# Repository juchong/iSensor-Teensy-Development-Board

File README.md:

# iSensor Teensy Development Board
### An open source development board for Analog Devices iSensor products

This development board was designed to provide users with an easy way to develop and test firmware using iSensor MEMS IMUs. The board conforms to the standard Arduino pinout making it compatible with the entire ecosystem of break-out boards. A Teensy 3.1, 3.2, or LC may be used with this board, minimizing cost. The board includes a standard 2mm pitch 16 pin connector similar to the BlackFin evaluation board, making all iSensor breakout boards compatible. 

The board includes the following features:
- 4V ~ 20V input, 3.3V output switching regulator with selectable input (USB vs External)
- Programmable high-side switch for controlled switching tests
- 3.3V external supply input
- I2C/Analog Input selectable solder pads
- Compatible with Arduino pinout and mechanical form factor

Note that the switching regulator is optional and does not have to be installed for the breakout board to properly function.

Click here to order a set of boards from OshPark: [https://oshpark.com/shared_projects/IdmggZVF](https://oshpark.com/shared_projects/IdmggZVF)

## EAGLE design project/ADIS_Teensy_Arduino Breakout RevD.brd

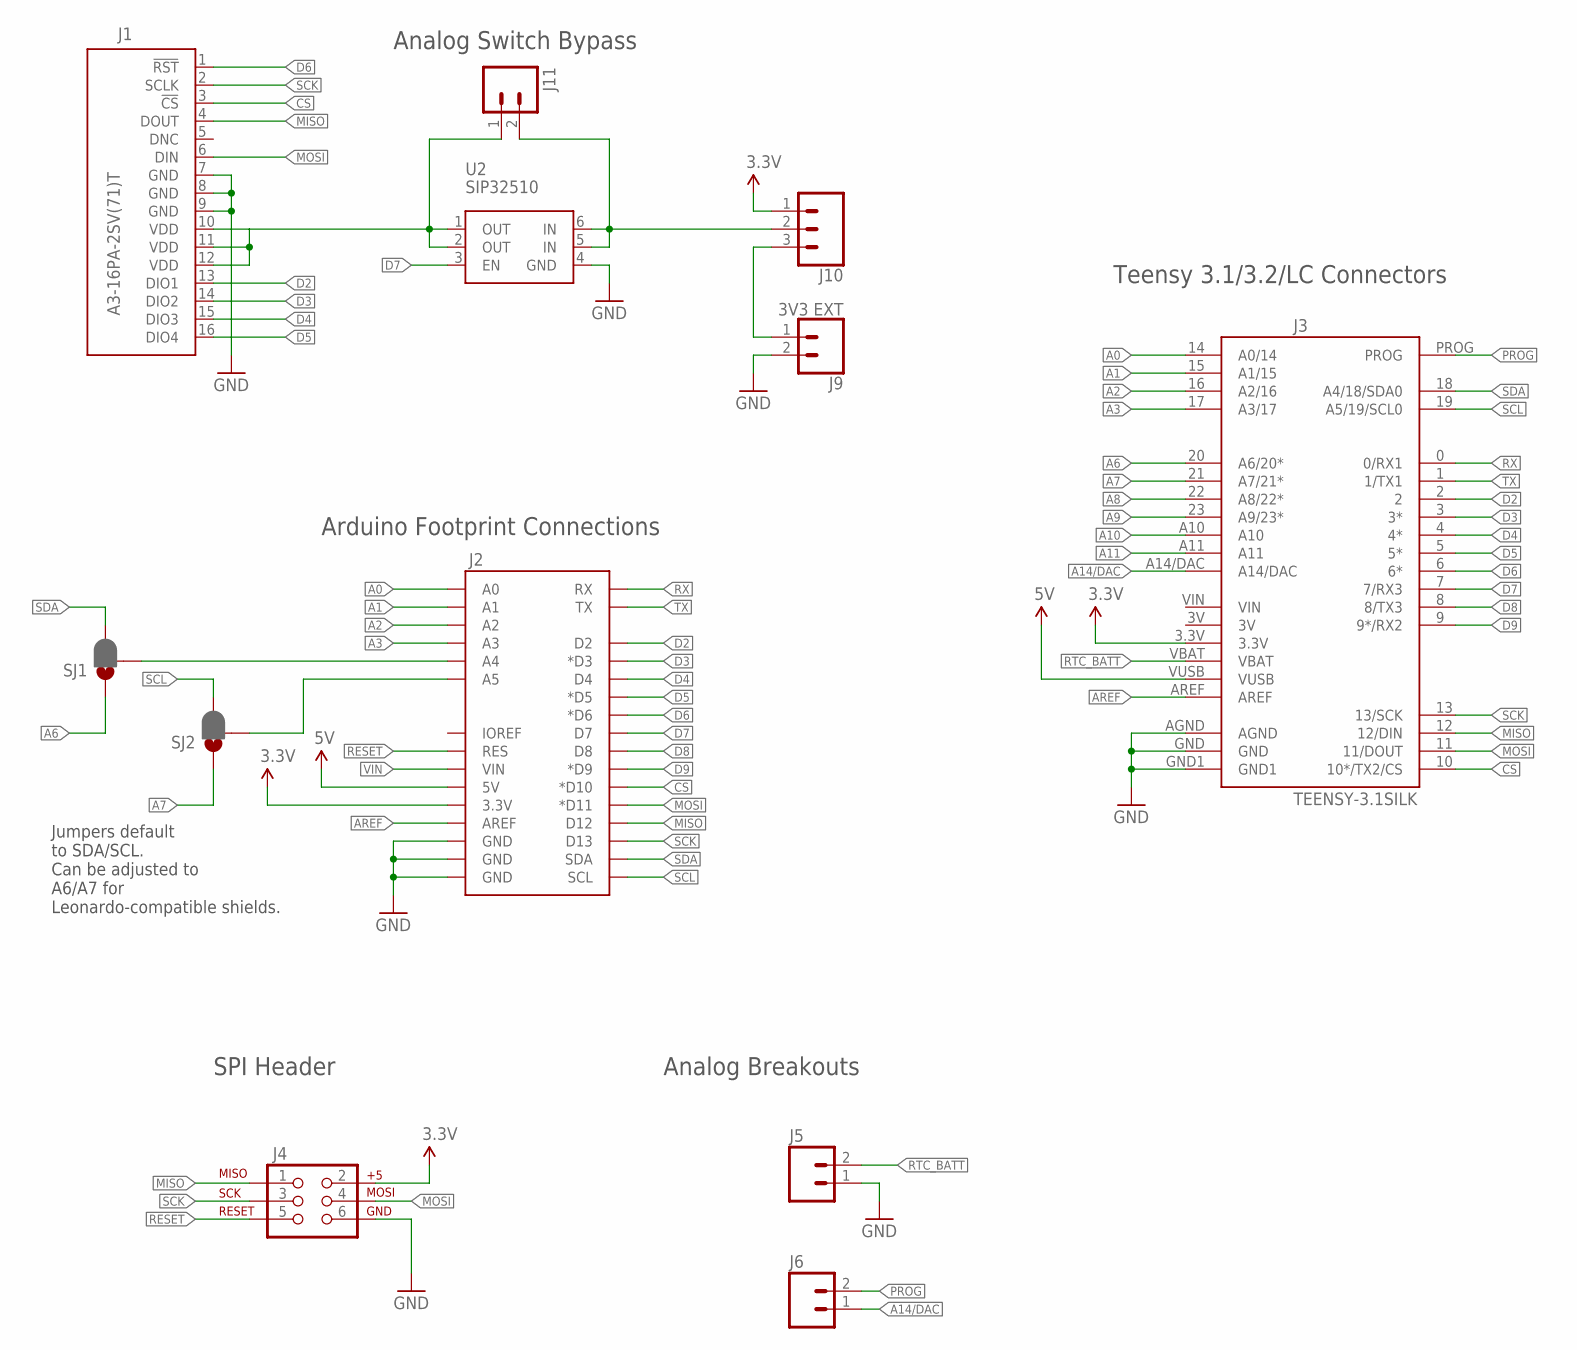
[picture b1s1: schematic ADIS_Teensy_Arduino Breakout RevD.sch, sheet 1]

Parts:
J1: A3-16PA-2SV(71)T; A3-16PA-2SV(71)-TOP; PARTNO A3-16PA-2SV(71)
J2: ARDUINO_R3_SHIELDUNO_R3_SHIELD_HOLES; UNO_R3_SHIELD_HOLES
J3: TEENSY-3.1SILK; TEENSY-3.1; PARTNO TEENSY32
J4: AVR_SPI_PRG_6PTH; 2X3; PARTNO M20-9720345
J5, J6, J11: M02PTH; 1X02@1
J9: 3V3 EXT; SCREWTERMINAL-3.5MM-2; PARTNO 20020327-C021B01LF
J10: CONN_03; 1X03; PARTNO 68000-103HLF
SJ1, SJ2: JUMPER-PAD-3-2OF3_NC_BY_PASTE; PAD-JUMPER-3-2OF3_NC_BY_PASTE_YES_SILK_FULL_BOX
U2: SIP32510; SOT23-6; PARTNO SIP32510DT-T1-GE3

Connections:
3.3V: J2.3.3V, J3.3.3V, J4.2, J10.1; also elsewhere on the board
5V: J2.5V, J3.VUSB; also elsewhere on the board
A0: J2.A0, J3.14 (A0/14)
A1: J2.A1, J3.15 (A1/15)
A2: J2.A2, J3.16 (A2/16)
A3: J2.A3, J3.17 (A3/17)
A4: J2.A4, SJ1.2
A5: J2.A5, SJ2.2
A6: J3.20 (A6/20*), SJ1.1
A7: J3.21 (A7/21*), SJ2.1
A8: J3.22 (A8/22*)
A9: J3.23 (A9/23*)
A10: J3.A10
A11: J3.A11
A14/DAC: J3.A14/DAC, J6.1
AREF: J2.AREF, J3.AREF
CS: J1.3 (!CS), J2.D10 (*D10), J3.10 (10*/TX2/CS)
D2: J1.13 (DIO1), J2.D2, J3.2
D3: J1.14 (DIO2), J2.D3 (*D3), J3.3 (3*)
D4: J1.15 (DIO3), J2.D4, J3.4 (4*)
D5: J1.16 (DIO4), J2.D5 (*D5), J3.5 (5*)
D6: J1.1 (!RST), J2.D6 (*D6), J3.6 (6*)
D7: J2.D7, J3.7 (7/RX3), U2.3 (EN)
D8: J2.D8, J3.8 (8/TX3)
D9: J2.D9 (*D9), J3.9 (9*/RX2)
GND: J1.7 (GND), J1.8 (GND), J1.9 (GND), J2.GND@0 (GND), J2.GND@1 (GND), J2.GND@2 (GND), J3.AGND, J3.GND, J3.GND1, J4.6, J5.1, J9.2, U2.4 (GND); also elsewhere on the board
MISO: J1.4 (DOUT), J2.D12, J3.12 (12/DIN), J4.1
MOSI: J1.6 (DIN), J2.D11 (*D11), J3.11 (11/DOUT), J4.4
unnamed: J1.10 (VDD), J1.11 (VDD), J1.12 (VDD), J11.1, U2.1 (OUT), U2.2 (OUT)
unnamed: J9.1, J10.3
unnamed: J10.2, J11.2, U2.5 (IN), U2.6 (IN)
PROG: J3.PROG, J6.2
RESET: J2.RES, J4.5
RTC_BATT: J3.VBAT, J5.2
RX: J2.RX, J3.0 (0/RX1)
SCK: J1.2 (SCLK), J2.D13, J3.13 (13/SCK), J4.3
SCL: J2.SCL, J3.19 (A5/19/SCL0), SJ2.3
SDA: J2.SDA, J3.18 (A4/18/SDA0), SJ1.3
TX: J2.TX, J3.1 (1/TX1)
VIN: J2.VIN; also elsewhere on the board

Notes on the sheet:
Jumpers default to SDA/SCL. Can be adjusted to A6/A7 for Leonardo-compatible shields.
Arduino Footprint Connections
SPI Header
Analog Breakouts
Teensy 3.1/3.2/LC Connectors
Analog Switch Bypass

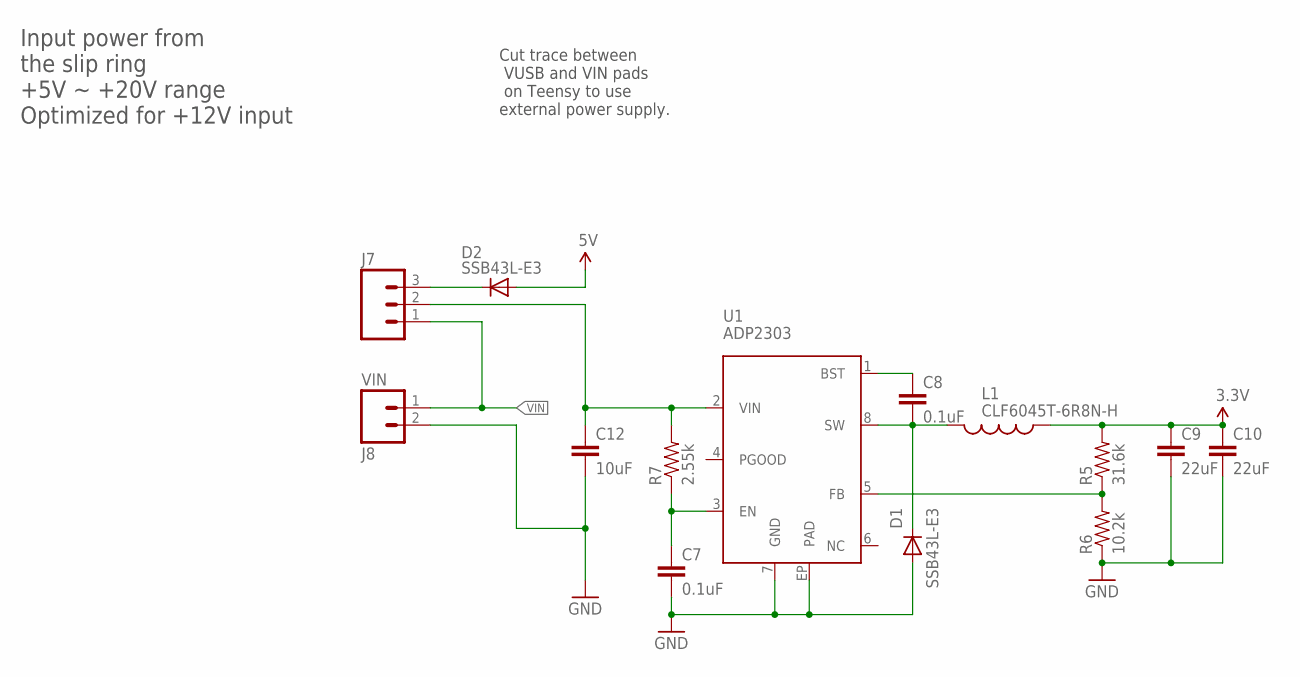
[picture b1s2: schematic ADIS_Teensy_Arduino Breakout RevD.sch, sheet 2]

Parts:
C7, C8: 0.1uF; 0603-CAP; PARTNO CL10B104KB8NNNC
C9, C10: 22uF; 1210; PARTNO TLJA476M010R0600
C12: 10uF; 1206; PARTNO TLJA476M010R0600
D1, D2: SSB43L-E3; DO214AA; PARTNO SSB43L-E3/52T
J7: M03PTH; 1X03@1; PARTNO 68000-103HLF
J8: VIN; SCREWTERMINAL-3.5MM-2@1; PARTNO 20020327-C021B01LF
L1: CLF6045T-6R8N-H; CLF6045-H; PARTNO CLF6045T-6R8N-H
R5: 31.6k; 0603-RES; PARTNO ERJ-3EKF3162V
R6: 10.2k; 0603-RES; PARTNO ERJ-3EKF1022V
R7: 2.55k; 0603-RES; PARTNO ERJ-3EKF2551V
U1: ADP2303; SOIC-8-PAD; PARTNO ADP2303ARDZ

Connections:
3.3V: C9.1, C10.1, L1.P$1 (1), R5.2; also elsewhere on the board
5V: D2.A; also elsewhere on the board
GND: C7.2, C9.2, C10.2, C12.2, D1.A, J8.2, R6.1, U1.7 (GND), U1.EP (PAD); also elsewhere on the board
unnamed: R5.1, R6.2, U1.5 (FB)
unnamed: C8.2, D1.C, L1.P$2 (2), U1.8 (SW)
unnamed: C8.1, U1.1 (BST)
unnamed: C7.1, R7.1, U1.3 (EN)
unnamed: C12.1, J7.2, R7.2, U1.2 (VIN)
unnamed: D2.C, J7.3
VIN: J7.1, J8.1; also elsewhere on the board

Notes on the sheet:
Input power from the slip ring +5V ~ +20V range Optimized for +12V input
Cut trace between VUSB and VIN pads on Teensy to use external power supply.

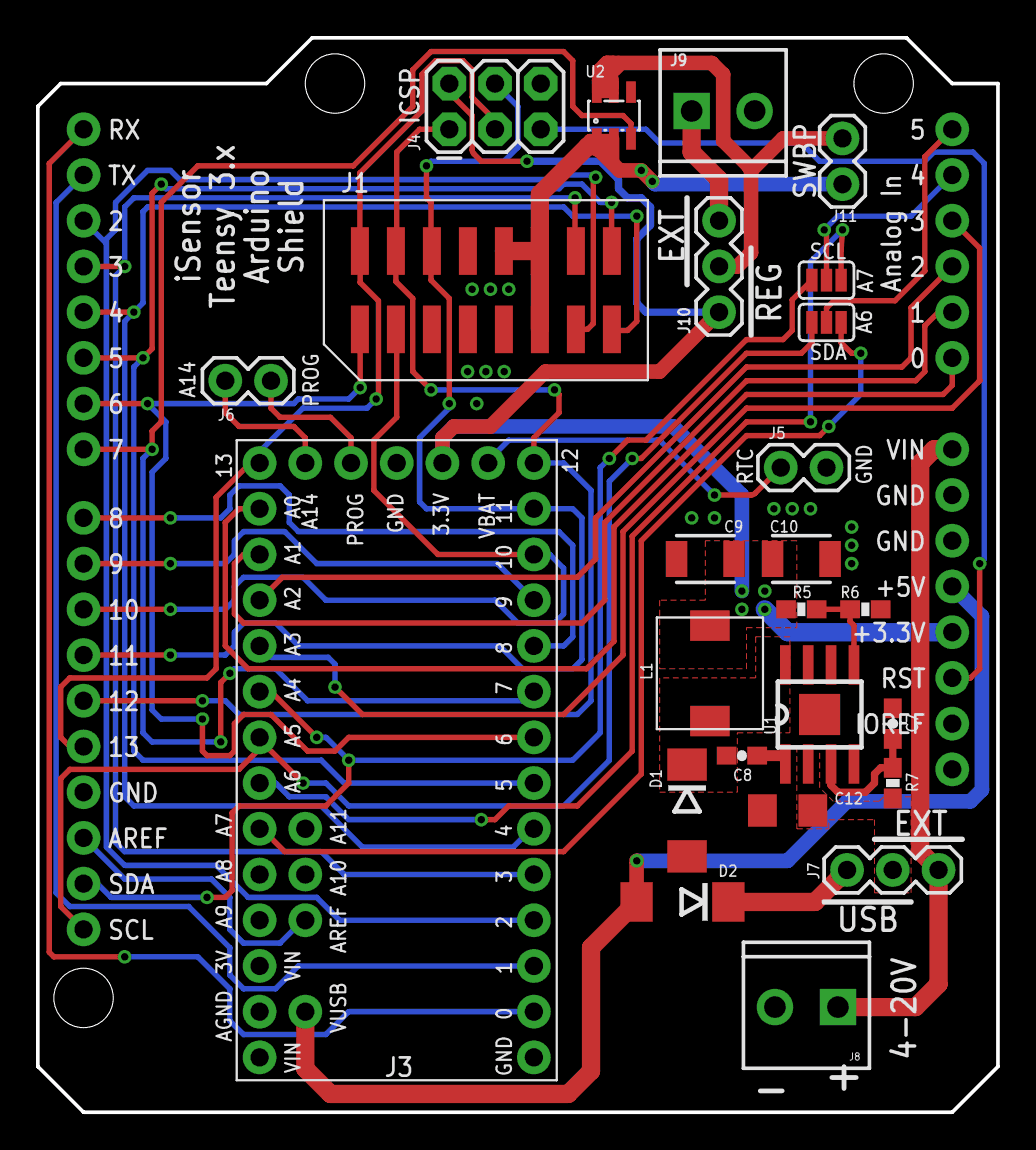
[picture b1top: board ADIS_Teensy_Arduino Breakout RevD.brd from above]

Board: 2 copper layers, 53.3 x 59.7 mm, 26 parts (0 on the bottom side), 42 nets.

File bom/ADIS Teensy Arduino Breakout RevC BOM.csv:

Qty-1,Part References,Value,Package,Mfg Part Num,Mfg Name,VID,Vendor Part Num,Description,Pkg Code,XREF
3,"J10, J7",,1X03,PRPC003SAAN-RC,Sullins Connector Solutions,DK,S1011EC-03-ND,"CONN HEADER .100"" SNGL STR 3POS",1X03,REF210
2,"C7, C8",0.1uF,0603-CAP,CL10B104KB8NNNC,Samsung Electro-Mechanics America,DK,1276-1000-1-ND,CAP CER 0.1UF 50V 10% X7R 0603,0603-CAP,REF134
1,R7,2.55k,0603-RES,ERJ-3EKF2551V,Panasonic Electronic Components,DK,P2.55KHCT-ND,RES SMD 2.55K OHM 1% 1/10W 0603,0603-RES,REF190
1,J9,3V3 EXT,SCREWTERMINAL-3.5MM-2,20020327-C021B01LF,FCI,DK,609-4725-ND,3.5MM TERMINAL BLOCK -55~110C,3.5MM,REF191
1,R6,10.2k,0603-RES,ERJ-3EKF1022V,Panasonic Electronic Components,DK,P10.2KHCT-ND,RES SMD 10.2K OHM 1% 1/10W 0603,0603-RES,REF189
3,"C12, C9, C10",22uF,1210,TLJA476M010R0600,AVX Corporation,DK,478-9009-1-ND,CAP TANT 47UF 10V 20% 1206,1206-RES,REF180
1,R5,31.6k,0603-RES,ERJ-3EKF3162V,Panasonic Electronic Components,DK,P31.6KHCT-ND,RES SMD 31.6K OHM 1% 1/10W 0603,0603-RES,REF188
1,J1,A3-16PA-2SV(71)T,A3-16PA-2SV(71)-TOP,A3-16PA-2SV(71),Hirose Electric Co Ltd,DK,H10940-ND,CONN HEADER 16POS 2MM GOLD SMD,2x8,REF201
1,U1,ADP2303,SOIC-8-PAD,ADP2303ARDZ,Analog Devices Inc,DK,ADP2303ARDZ-ND,IC REG BUCK ADJ 3A 8SOIC,8-SOIC-EP,REF186
1,J4,AVR_SPI_PRG_6PTH,2X3,M20-9720345,Harwin Inc,DK,952-1921-ND,2X3POS DIL VERTICAL PIN HEADER,2x3,REF203
1,L1,CLF6045T-6R8N-H,CLF6045-H,CLF6045T-6R8N-H,TDK Corporation,DK,445-15108-1-ND,FIXED IND 6.8UH 2.9A 27 MOHM SMD,INDUCTOR,REF204
1,U2,SIP32510,SOT23-6,SIP32510DT-T1-GE3,Vishay Siliconix,DK,SIP32510DT-T1-GE3CT-ND,IC LOAD SWITCH SOT23-6,SOT23-6,REF205
2,"D1, D2",SSB43L-E3,DO214AA,SSB43L-E3/52T,Vishay Semiconductor Diodes Division,DK,SSB43L-E3/52TGICT-ND,DIODE SCHOTTKY 30V 4A DO214AA,DO-214AA,REF181
1,J3,TEENSY-3.1SILK,TEENSY-3.1,TEENSY32,pjrc.com,pjrc.com,TEENSY32,Teensy USB Board Version 3.2,TEENSY,REF202
1,J8,VIN,SCREWTERMINAL-3.5MM-2@1,20020327-C021B01LF,FCI,DK,609-4725-ND,3.5MM TERMINAL BLOCK -55~110C,3.5MM,REF191
2,,,1x14,PRPC014SAAN-RC,Sullins Connector Solutions,DK,S1011EC-14-ND,"CONN HEADER .100"" SNGL STR 14POS",1x14,REF208
1,,,1x05,PRPC005SAAN-RC,Sullins Connector Solutions,DK,S1011EC-05-ND,"CONN HEADER .100"" SNGL STR 5POS",1x05,REF209
1,,,1x01,PRPC001SAAN-RC,Sullins Connector Solutions,DK,S1011EC-01-ND,"CONN HEADER .100"" SNGL STR 1POS",1x01,REF211
2,,,1x14,PPPC141LFBN-RC,Sullins Connector Solutions,DK,S7047-ND,"CONN HEADER FMALE 14POS .1"" GOLD",1x14,REF212
1,,,1x05,PPPC051LFBN-RC,Sullins Connector Solutions,DK,S7038-ND,"CONN HEADER FEMALE 5POS .1"" GOLD",1x05,REF213
2,,,1x08,PPPC081LFBN-RC,Sullins Connector Solutions,DK,S7041-ND,"CONN HEADER FEMALE 8POS .1"" GOLD",1x08,REF214
1,,,1x10,PPPC101LFBN-RC,Sullins Connector Solutions,DK,S7043-ND,"CONN HEADER FEMALE 10POS .1"" GOLD",1x10,REF215
1,,,1x06,PPPC061LFBN-RC,Sullins Connector Solutions,DK,S7039-ND,"CONN HEADER FEMALE 6POS .1"" GOLD",1x06,REF216
1,,,1x03,PPPC031LFBN-RC,Sullins Connector Solutions,DK,S7036-ND,"CONN HEADER FEMALE 3POS .1"" GOLD",1x03,REF217
2,,,JUMPER,SPC02SYAN,Sullins Connector Solutions,DK,S9001-ND,CONN JUMPER SHORTING GOLD FLASH,JUMPER,REF218

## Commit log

2017-12-20 Initial Rev C commit
2017-12-20 Updated BOM in brd and sch files
2019-02-07 Updated PCB to Rev D
2019-02-07 Updated Readme with new PCB link

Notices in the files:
parts and their libraries:
SparkFun-Connectors: Licensing: Creative Commons ShareAlike 4.0 International - https://creativecommons.org/licenses/by-sa/4.0
